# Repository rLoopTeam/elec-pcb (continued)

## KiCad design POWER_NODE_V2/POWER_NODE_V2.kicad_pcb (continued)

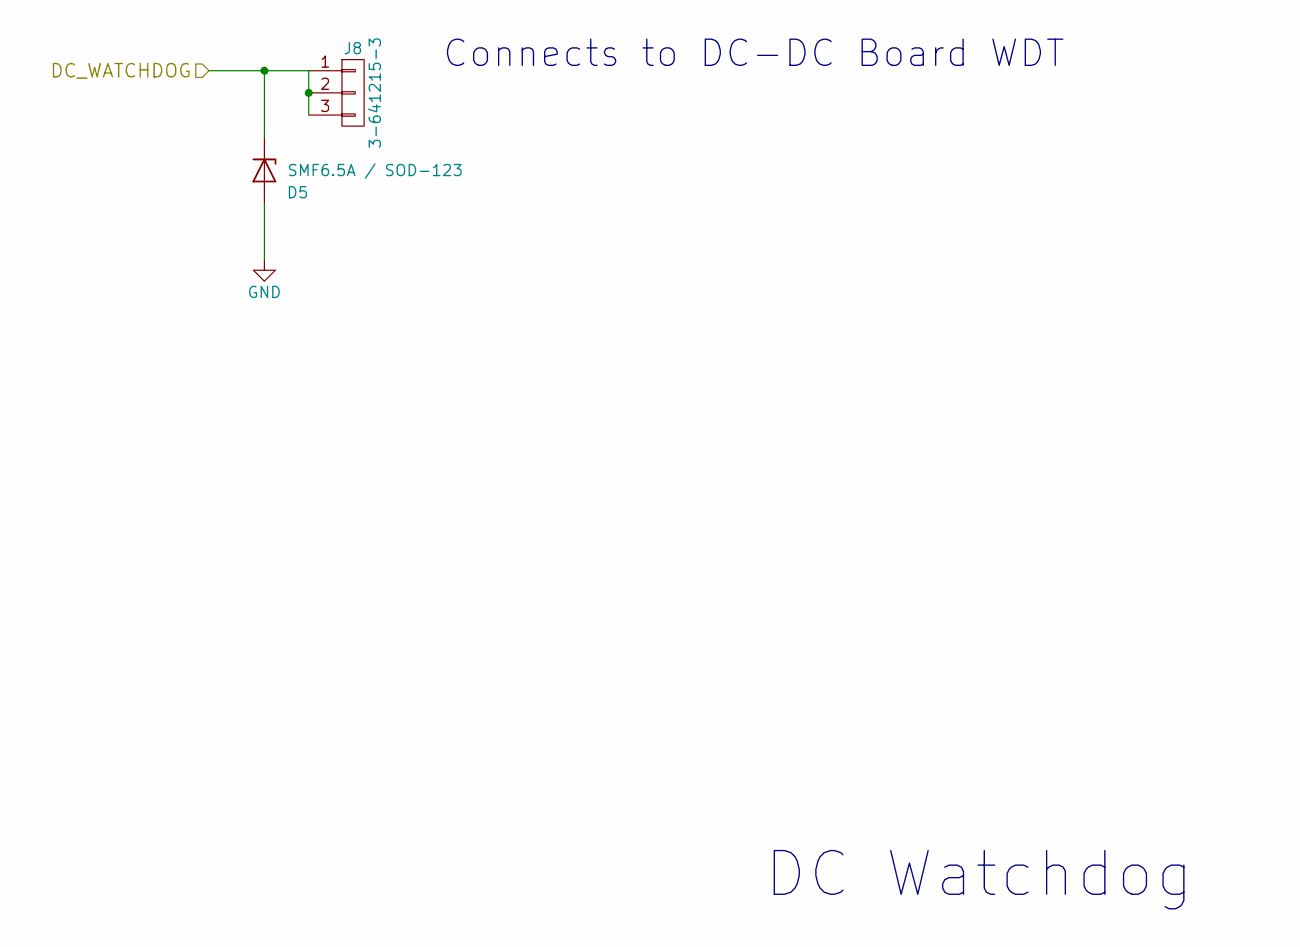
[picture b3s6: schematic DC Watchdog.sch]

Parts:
D5: SMF6.5A / SOD-123; D_SOD-123
J8: 3-641215-3; 3-641215-3_3Pin_Latching_Header

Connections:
/DC Watchdog/DC_WATCHDOG: D5.1 (K), J8.1, J8.2, J8.3; also elsewhere on the board
GND: D5.2 (A); also elsewhere on the board

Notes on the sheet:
Connects to DC-DC Board WDT
DC Watchdog

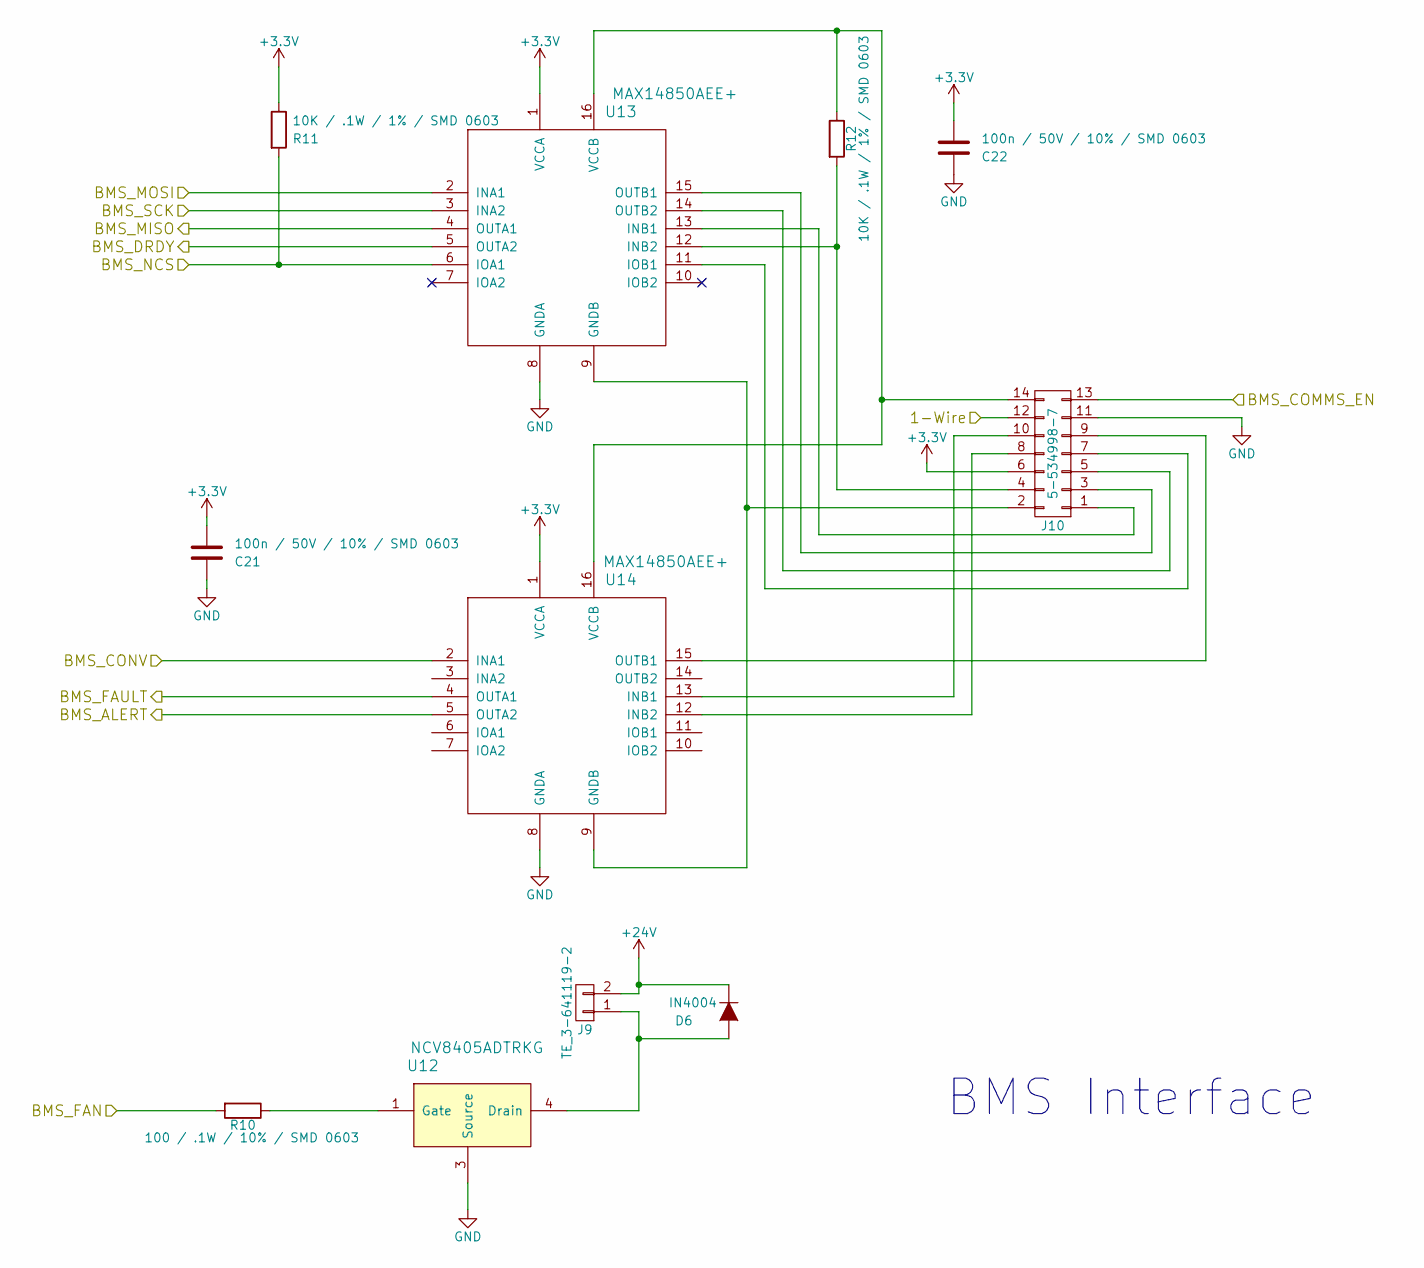
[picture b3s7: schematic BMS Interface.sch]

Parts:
C21, C22: 100n / 50V / 10% / SMD 0603; C_0603
D6: IN4004; D_DO-201_P15.24mm_Horizontal
J9: TE_3-641119-2; 3-641119-2_TE_2P_MTA156_HDR
J10: 5-534998-7; Pin_Header_Straight_2x07_Pitch2.54mm
R10: 100 / .1W / 10% / SMD 0603; R_0603
R11, R12: 10K / .1W / 1% / SMD 0603; R_0603
U12: NCV8405ADTRKG; SOT-223
U13, U14: MAX14850AEE+; QSOP-16_3.9x4.9mm_Pitch0.635mm

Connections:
+24V: D6.1 (K), J9.2; also elsewhere on the board
/BMS Interface/1-Wire: J10.12; also elsewhere on the board
/BMS Interface/BMS_ALERT: U14.5 (OUTA2); also elsewhere on the board
/BMS Interface/BMS_COMMS_EN: J10.13; also elsewhere on the board
/BMS Interface/BMS_CONV: U14.2 (INA1); also elsewhere on the board
/BMS Interface/BMS_DRDY: U13.5 (OUTA2); also elsewhere on the board
/BMS Interface/BMS_FAN: R10.2; also elsewhere on the board
/BMS Interface/BMS_FAULT: U14.4 (OUTA1); also elsewhere on the board
/BMS Interface/BMS_MISO: U13.4 (OUTA1); also elsewhere on the board
/BMS Interface/BMS_MOSI: U13.2 (INA1); also elsewhere on the board
/BMS Interface/BMS_NCS: R11.2, U13.6 (IOA1); also elsewhere on the board
/BMS Interface/BMS_SCK: U13.3 (INA2); also elsewhere on the board
GND: C21.2, C22.2, J10.11, U12.3 (Source), U13.8 (GNDA), U14.8 (GNDA); also elsewhere on the board
unnamed: D6.2 (A), J9.1, U12.4 (Drain)
unnamed: J10.1, U13.13 (INB1)
unnamed: J10.2, U13.9 (GNDB), U14.9 (GNDB)
unnamed: J10.3, U13.15 (OUTB1)
unnamed: J10.4, R12.2, U13.12 (INB2)
unnamed: J10.5, U13.14 (OUTB2)
unnamed: J10.7, U13.11 (IOB1)
unnamed: J10.8, U14.12 (INB2)
unnamed: J10.9, U14.15 (OUTB1)
unnamed: J10.10, U14.13 (INB1)
unnamed: J10.14, R12.1, U13.16 (VCCB), U14.16 (VCCB)
unnamed: R10.1, U12.1 (Gate)

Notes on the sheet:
BMS Interface

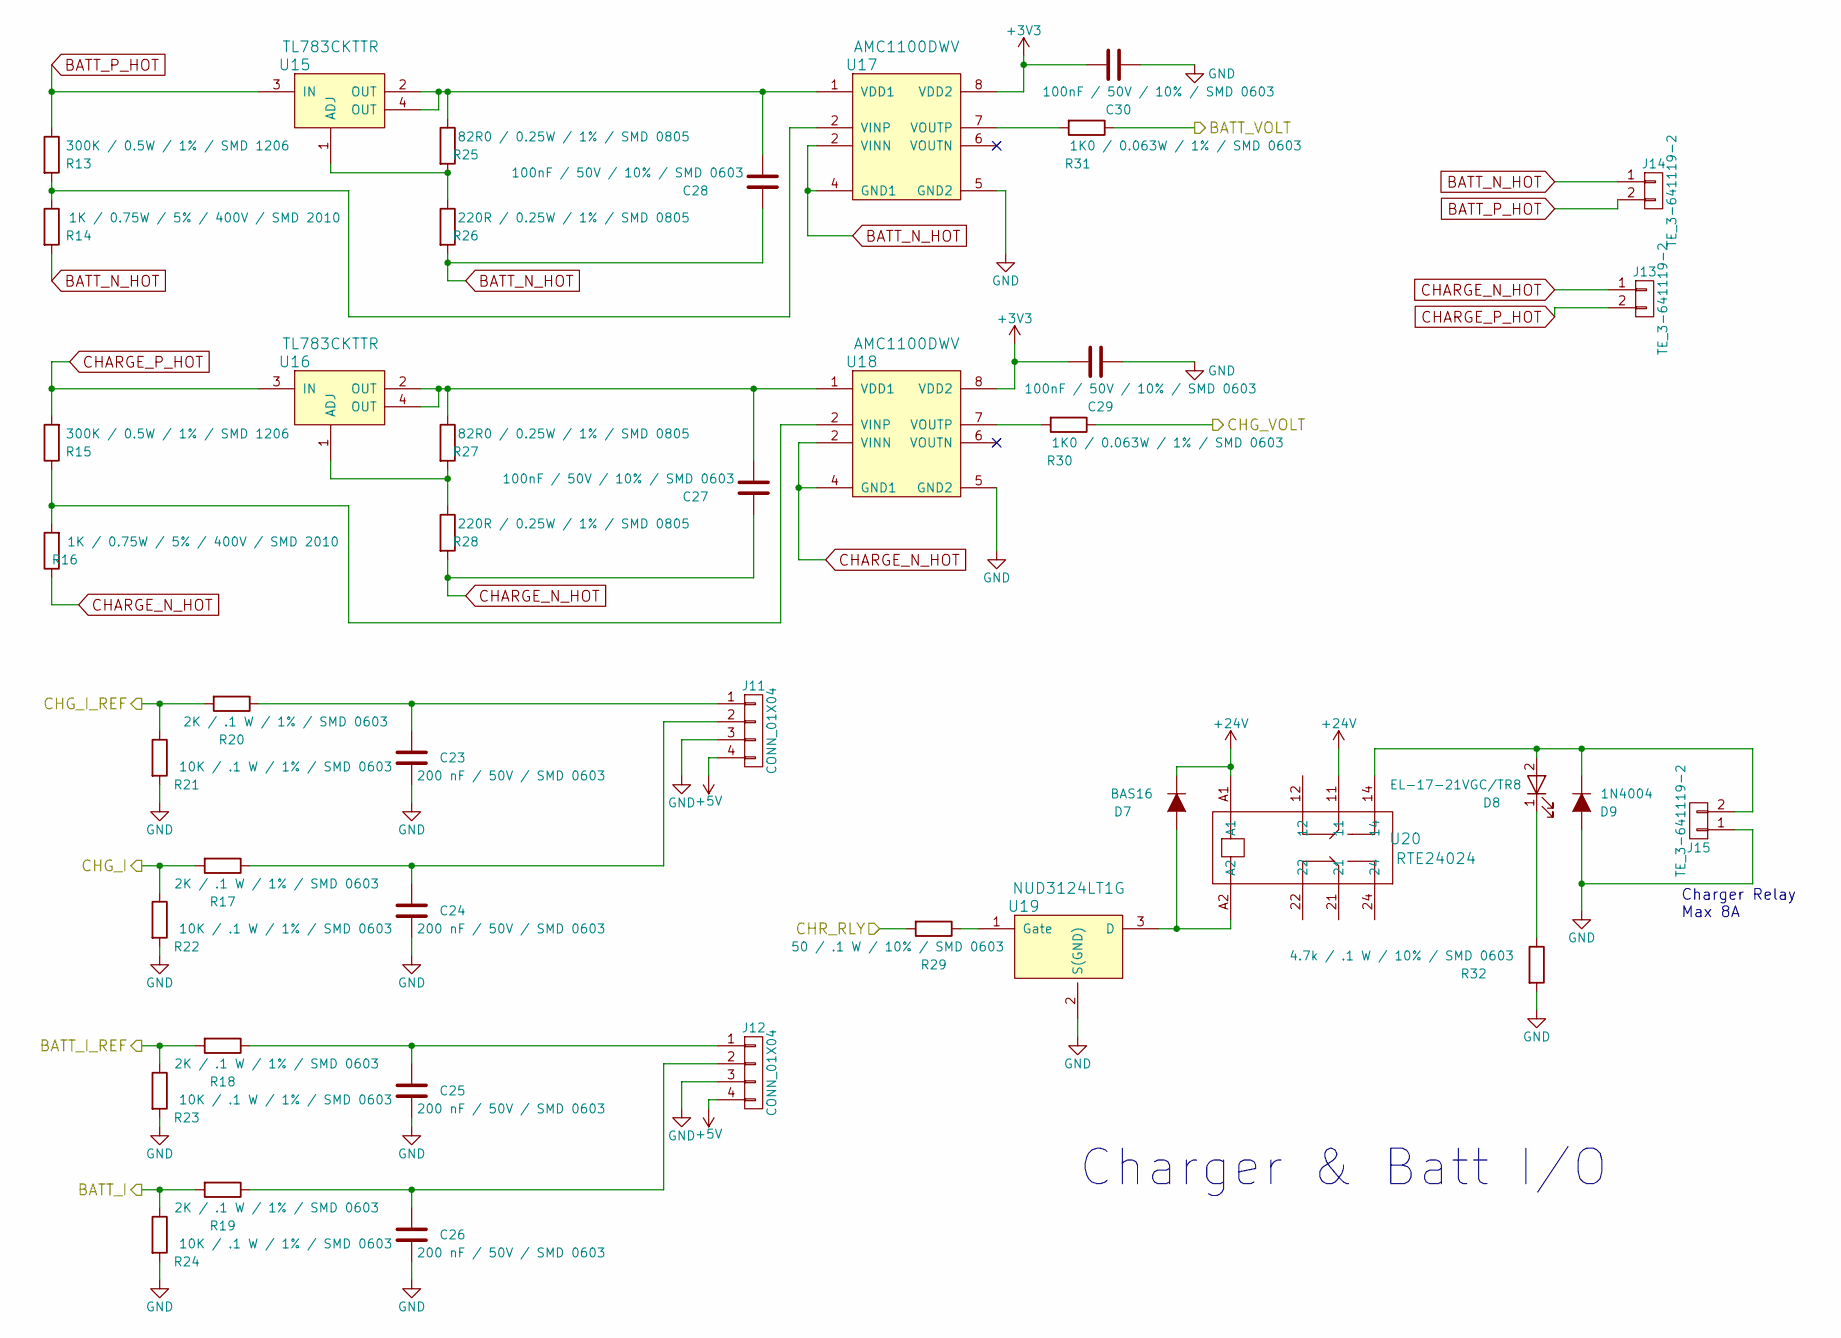
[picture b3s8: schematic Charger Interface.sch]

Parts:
C23, C24, C25, C26: 200 nF / 50V / SMD 0603; C_0603
C27, C28, C29, C30: 100nF / 50V / 10% / SMD 0603; C_0603
D7: BAS16; D_SOT-23_ANK
D8: EL-17-21VGC/TR8; LED_0805
D9: 1N4004; D_DO-201_P15.24mm_Horizontal
J11, J12: CONN_01X04; 22-04-1041_Molex_4_Pin_Header_2.50mm
J13, J14, J15: TE_3-641119-2; 3-641119-2_TE_2P_MTA156_HDR
R13, R15: 300K / 0.5W / 1% / SMD 1206; R_1206
R14, R16: 1K / 0.75W / 5% / 400V / SMD 2010; R_2010
R17, R18, R19, R20: 2K / .1 W / 1% / SMD 0603; R_0603
R21, R22, R23, R24: 10K / .1 W / 1% / SMD 0603; R_0603
R25, R27: 82R0 / 0.25W / 1% / SMD 0805; R_0805
R26, R28: 220R / 0.25W / 1% / SMD 0805; R_0805
R29: 50 / .1 W / 10% / SMD 0603; R_0603
R30, R31: 1K0 / 0.063W / 1% / SMD 0603; R_0603
R32: 4.7k / .1 W / 10% / SMD 0603; R_0603
U15, U16: TL783CKTTR; tl783ckttr
U17, U18: AMC1100DWV; amc1100_SOIC8
U19: NUD3124LT1G; SOT-23
U20: RTE24024

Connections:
+5V: J11.4, J12.4; also elsewhere on the board
+24V: D7.1 (K), U20.11, U20.A1; also elsewhere on the board
/Charger Interface/BATT_I: R19.2, R24.1; also elsewhere on the board
/Charger Interface/BATT_I_REF: R18.2, R23.1; also elsewhere on the board
/Charger Interface/BATT_VOLT: R31.1; also elsewhere on the board
/Charger Interface/CHG_I: R17.2, R22.1; also elsewhere on the board
/Charger Interface/CHG_I_REF: R20.2, R21.1; also elsewhere on the board
/Charger Interface/CHG_VOLT: R30.1; also elsewhere on the board
/RM57 Core/CHG_RLY: R29.2; also elsewhere on the board
BATT_P_HOT: J14.2, R13.1, U15.3 (IN)
CHARGE_P_HOT: J13.2, R15.2, U16.3 (IN)
GND: C23.2, C24.2, C25.2, C26.2, C29.1, C30.1, D9.2 (A), J11.3, J12.3, J15.1, R21.2, R22.2, R23.2, R24.2, R32.2, U17.5 (GND2), U18.5 (GND2), U19.2 (S(GND)); also elsewhere on the board
unnamed: C23.1, J11.1, R20.1
unnamed: C24.1, J11.2, R17.1
unnamed: C25.1, J12.1, R18.1
unnamed: C26.1, J12.2, R19.1
unnamed: C27.1, R27.1, U16.2 (OUT), U16.4 (OUT), U18.1 (VDD1)
unnamed: C28.2, R25.1, U15.2 (OUT), U15.4 (OUT), U17.1 (VDD1)
unnamed: D7.2 (A), U19.3 (D), U20.A2
unnamed: D8.1 (K), R32.1
unnamed: D8.2 (A), D9.1 (K), J15.2, U20.14
unnamed: R25.2, R26.1, U15.1 (ADJ)
unnamed: R27.2, R28.1, U16.1 (ADJ)
unnamed: R29.1, U19.1 (Gate)
unnamed: R30.2, U18.7 (VOUTP)
unnamed: R31.2, U17.7 (VOUTP)

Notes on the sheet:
Charger Relay Max 8A
Charger & Batt I/O

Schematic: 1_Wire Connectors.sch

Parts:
J16, J17, J18, J19, J20, J21: 3-641215-3; 3-641215-3_3Pin_Latching_Header

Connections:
/1-Wire Connectors/ONE_WIRE_BATT_1_3: J16.2; also elsewhere on the board
/1-Wire Connectors/ONE_WIRE_BATT_4_6: J17.2; also elsewhere on the board
/1-Wire Connectors/ONE_WIRE_BATT_7_9: J18.2; also elsewhere on the board
/1-Wire Connectors/ONE_WIRE_BATT_10_12: J19.2; also elsewhere on the board
/1-Wire Connectors/ONE_WIRE_BATT_13_15: J20.2; also elsewhere on the board
/1-Wire Connectors/ONE_WIRE_BATT_16_18: J21.2; also elsewhere on the board
GND: J16.3, J17.3, J18.3, J19.3, J20.3, J21.3; also elsewhere on the board

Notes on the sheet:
1-Wire Connectors to Battery

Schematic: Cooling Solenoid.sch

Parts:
D13: BAS16; D_SOT-23_ANK
D14: EL-17-21VGC/TR8; LED_0805
D15: 1N4004
P1: TE_3-641119-2; 3-641119-2_TE_2P_MTA156_HDR
R33: 50 / .1 W / 10% / SMD 0603; R_0603
R34: 4.7k / .1W / 10% / SMD 0603; R_0603
U21: NUD3124LT1G; SOT-23
U22: RTE24024

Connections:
+24V: D13.1 (K), U22.11, U22.A1; also elsewhere on the board
/Cooling_Solenoid/COOLING_SOLENOID: R33.2; also elsewhere on the board
GND: D15.2 (A), P1.1, R34.2, U21.2 (S(GND)); also elsewhere on the board
unnamed: D13.2 (A), U21.3 (D), U22.A2
unnamed: D14.1 (K), R34.1
unnamed: D14.2 (A), D15.1 (K), P1.2, U22.14
unnamed: R33.1, U21.1 (Gate)

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
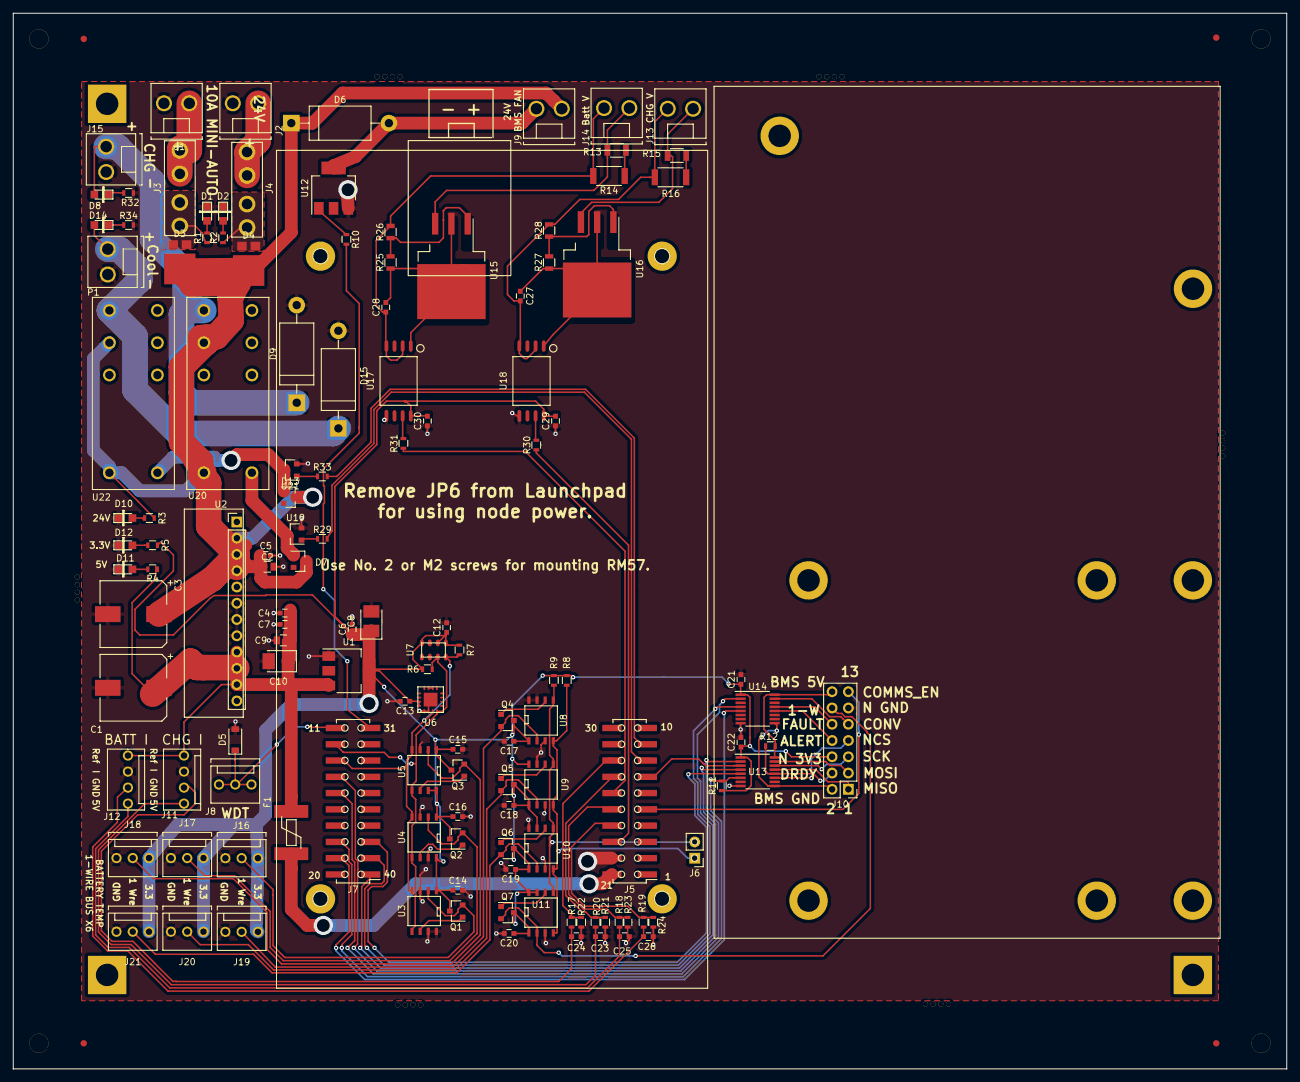
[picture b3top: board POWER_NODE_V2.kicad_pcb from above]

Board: 2 copper layers, 198.8 x 164.8 mm, 134 parts (0 on the bottom side), 88 nets.

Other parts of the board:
BMS_Outline: BMS_Outline
Power_Node_Mounting_Holes: Power_Node_Mounting_Holes
RM57_Mounting_Holes: RM57_Mounting_Holes; RM57_Mounting_Hole
RM_57_Outline: RM57_Launchpad_Outline

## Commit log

2016-07-18 Initial commit of Command Node and Control Node completed designs.
2016-07-18 Initial commit of the 16 channel thermal interface module.
2016-07-18 Initial commit of the high current sensor.
2016-07-18 Initial commit of the DC/DC converter, power distribution and fuse module.
2016-07-18 Initial commit of remote accelerometer module.
2016-07-18 Initial commit of the battery management system pod.
2016-07-18 Initial commit of node core.
2016-07-18 Initial commit of gimbal control hardware.
2016-07-18 Initial commit of gimbal interface module.
2016-07-20 Initial commit of redundant brake controller.
2016-08-16 Update across all boards.
    Test points.
    Completion of Power Node
    Completion of Battery Pack Module
    Updated contrast sensor interface
    3D Inventor files of PCB assemblies.
2016-09-06 Add RM48 Version of Power control Node.
2016-10-16 Initial commit of Flight Control Unit.
2016-10-16 Refresh PDF outputs.
2016-10-22 Final of Flight Control Unit.
2017-01-31 Updated PCB's per hardware used for SpaceX test week.
2017-05-12 Initial Commit of BMS v2
    Schematics mostly done. Need to check a few pinouts as noted in the
    drawings. Next step: PCBs.
2017-05-13 Bug Fixes
    A few fixes and cleanup to make the ERC happy.
2017-05-14 Footprint work
    starting to assign footprints to parts
2017-05-14 footprint and layout work WIP
2017-05-15 board layout wip
2017-05-15 PCB Layout WIP
2017-05-19 more PCB layout work
2017-05-21 more PCB work on BMS v2
2017-05-23 BMS v2 PCB work
    almost done, mostly need to check stencil
2017-05-24 BMS v2 fixed a few traces
2017-05-25 More PCB work on BMS v2
    lined up parts with the power node board
2017-05-28 More PCB Work
    Should be done, needs final check on the stencil and solder mask around
    the ata6870 thermal pad
2017-05-28 WIP
    See if it's even possible
2017-05-30 Ti BMS WIP
    Getting there. Need to add temp sensors, fan control, and an LDO for the
    SPI ISO supply.
2017-05-30 WIP
    not sure about these files. crashed KiCad turning off windows :/ Should
    all be there though.
2017-05-30 more weirdness
    dunno, looks ok though.
2017-05-31 More WIP on BMS v2.5
2017-05-31 More BMS v2.5 WIP
2017-06-07 more WIP
    making room for a thermal pad and power circuits
2017-06-16 BMS v2.5 more WIP
    so close, all traces routed.
2017-06-18 more WIP
    TODO:
    Fix pin 50
    ground planes
    figure out GND_2 weirdness
    fix optoisolator 3d model
    bq IC 3d model
2017-06-19 More WIP
    Added connector for 1-Wire sensors if we want to put some sensors on the
    heat-sinks. Just need to double check everything with the 3d-models.
2017-06-19 more WIP
    So close. Need to finish arranging the sild screen and make sure diodes
    get put on in the correct orientation.
2017-06-20 BMS v2.5 should be ready to go, want to triple check things in the AM
2017-06-21 Added BOM, added pin 1 markings on a few parts
2017-06-21 Change 2 Ohm Resistor
    Had to change for heatsink mounting :/
2017-06-21 Relowed fills in KiCad
2017-06-22 WIP - I2C bus laid out
2017-06-24 WIP
    making good progress
2017-06-24 Removed dup files
2017-06-24 Updated page sizes for schematics
2017-06-24 change Q1 transistor
    Fixing something out of stock
2017-06-25 more wip
2017-06-26 Power Node V2 WIP
2017-06-27 Schematic for Power Node V2 mostly done - mostly need connectors
2017-06-27 Add Gnd to power inputs
    oops.
2017-06-27 made a lot of footprints, began PCB layout for power node v2
2017-06-29 Power Node v2 WIP
    TODO: 3d models, double check everything, update connector P/N on
    schematics, align boards and drill holes
2017-06-30 3d WIP
2017-06-30 3d model work
    TODO: change 2 pins to MTA156
2017-07-02 Lot's of progress
2017-07-04 All modelled, schematics and mechanical just need a double check
2017-07-04 Windows doesn't like spaces
2017-07-05 swapped a few connectors to standardize with the power node and what's readily available
2017-07-05 added some text to the silk screen
2017-07-12 Added tooling holes & fiducial marks
2017-07-12 remove old pdf
2017-07-13 added cooling solenoid to pcb
2017-07-16 Added tooling and fiducial holes to BMS
2017-07-17 [new] Lots of new PCB's
2017-07-18 Gerbers, drill files, and current PDF.
2017-07-18 Gerbers, drill files and current schematics
2017-07-18 added titles on pcb
2017-07-18 Add BOM
2017-07-19 fix pdf
2017-07-19 Old version, removing for clarity
2017-07-20 Added Eco1 gerber layer for BMS
2017-07-23 Charger IF WIP
2017-07-24 Added URLS WIP
2017-07-25 Rough start on charger IF PCB
2017-07-26 added notes from 1st runs
2017-07-27 Charger IF WIP
    Mostly just need to double check all the mechanics and add a few
    mounting holes
2017-07-27 updated to osh park design rules
2017-07-28 Charger IF
    Just need to do a once over before ordering
2017-07-31 Charger IF
    needs double checking and pin labels on silkscreen
2017-07-31 Final Charger IF
2017-07-31 Finals w/ pdf
2017-08-01 U7 missing ground note
2017-08-02 BMS V2 build notes update
2017-08-03 Cleaned up PN for BOM
    need exact PN for excel sheet on one or two items.
2017-08-08 fix arduino board header hole sizes
